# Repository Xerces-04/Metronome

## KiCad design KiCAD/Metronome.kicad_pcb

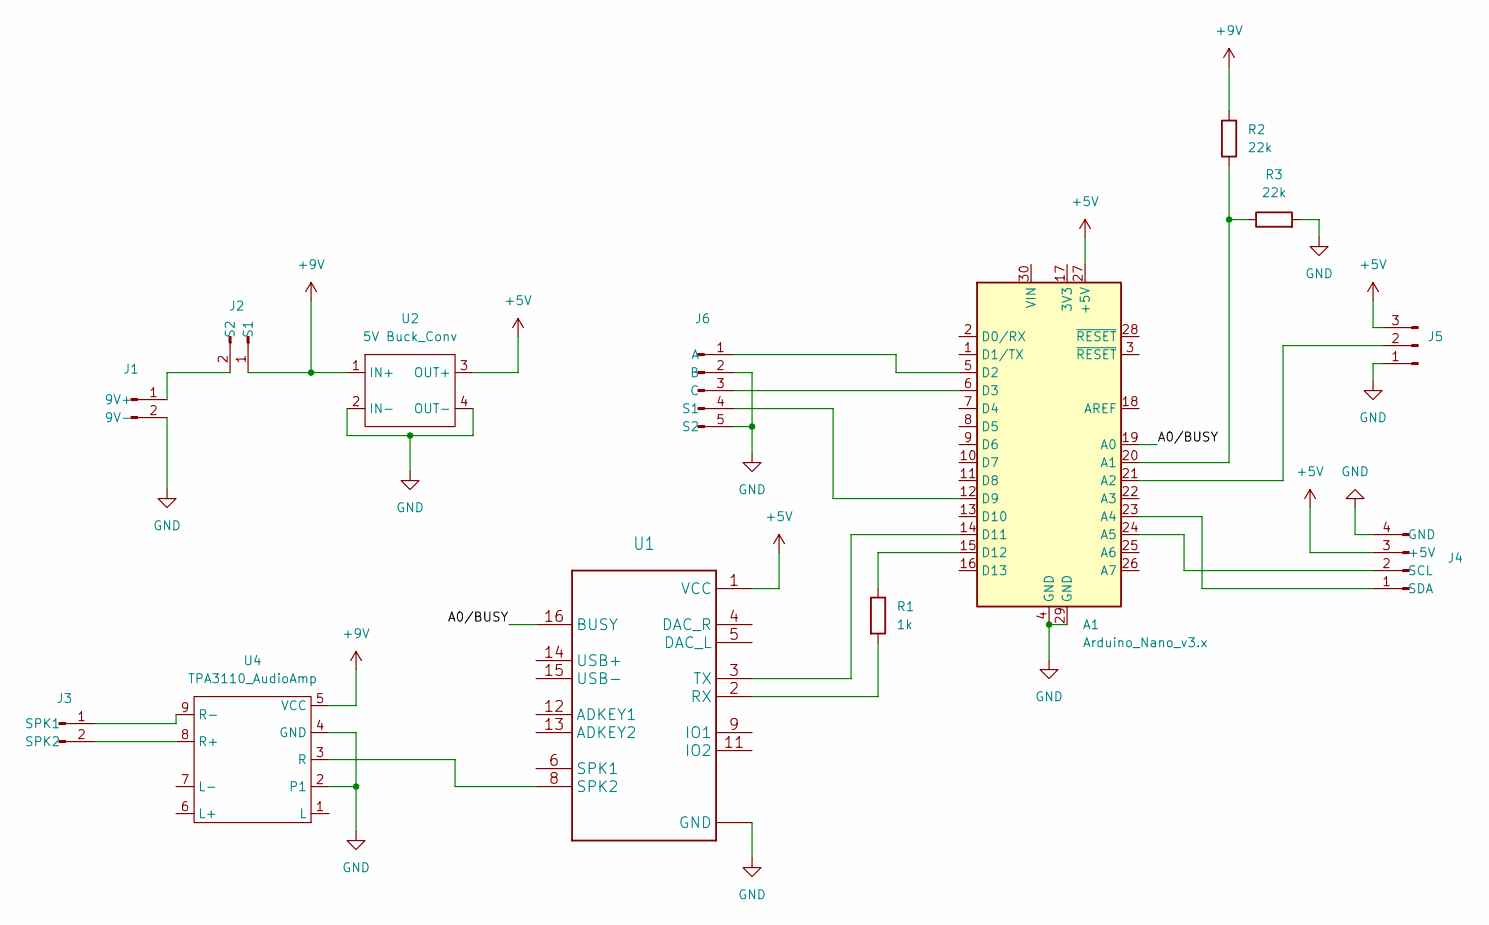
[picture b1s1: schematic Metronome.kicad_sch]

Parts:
A1: Arduino_Nano_v3.x; Arduino_Nano
J1, J2, J3: Conn_01x02_Pin; JST_XH_B2B-XH-A_1x02_P2.50mm_Vertical
J4: Conn_01x04_Pin; JST_XH_B4B-XH-A_1x04_P2.50mm_Vertical
J5: Conn_01x03_Pin; JST_XH_B3B-XH-A_1x03_P2.50mm_Vertical
J6: Conn_01x05_Pin; JST_XH_B5B-XH-A_1x05_P2.50mm_Vertical
R1: 1k; R_Axial_DIN0204_L3.6mm_D1.6mm_P7.62mm_Horizontal
R2, R3: 22k; R_Axial_DIN0204_L3.6mm_D1.6mm_P7.62mm_Horizontal
U1: MODULE_DFR0299
U2: 5V Buck_Conv; 5V_BuckConv
U4: TPA3110_AudioAmp

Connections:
+5V: A1.27 (+5V), J4.3 (+5V), J5.3, U1.1 (VCC), U2.3 (OUT+)
+9V: J2.1 (S1), R2.2, U2.1 (IN+), U4.5 (VCC)
/A0/BUSY: A1.19 (A0), U1.16 (BUSY)
GND: A1.4 (GND), A1.29 (GND), J1.2 (9V-), J4.4 (GND), J5.1, J6.2 (B), J6.5 (S2), R3.2, U1.7 (GND), U1.10 (GND), U2.2 (IN-), U2.4 (OUT-), U4.2 (P1), U4.4 (GND)
unnamed: A1.20 (A1), R2.1, R3.1
unnamed: A1.21 (A2), J5.2
unnamed: A1.23 (A4), J4.1 (SDA)
unnamed: A1.24 (A5), J4.2 (SCL)
unnamed: A1.5 (D2), J6.1 (A)
unnamed: A1.6 (D3), J6.3 (C)
unnamed: A1.12 (D9), J6.4 (S1)
unnamed: A1.14 (D11), U1.3 (TX)
unnamed: A1.15 (D12), R1.1
unnamed: J1.1 (9V+), J2.2 (S2)
unnamed: J3.1 (SPK1), U4.9 (R-)
unnamed: J3.2 (SPK2), U4.8 (R+)
unnamed: R1.2, U1.2 (RX)
unnamed: U1.8 (SPK2), U4.3 (R)

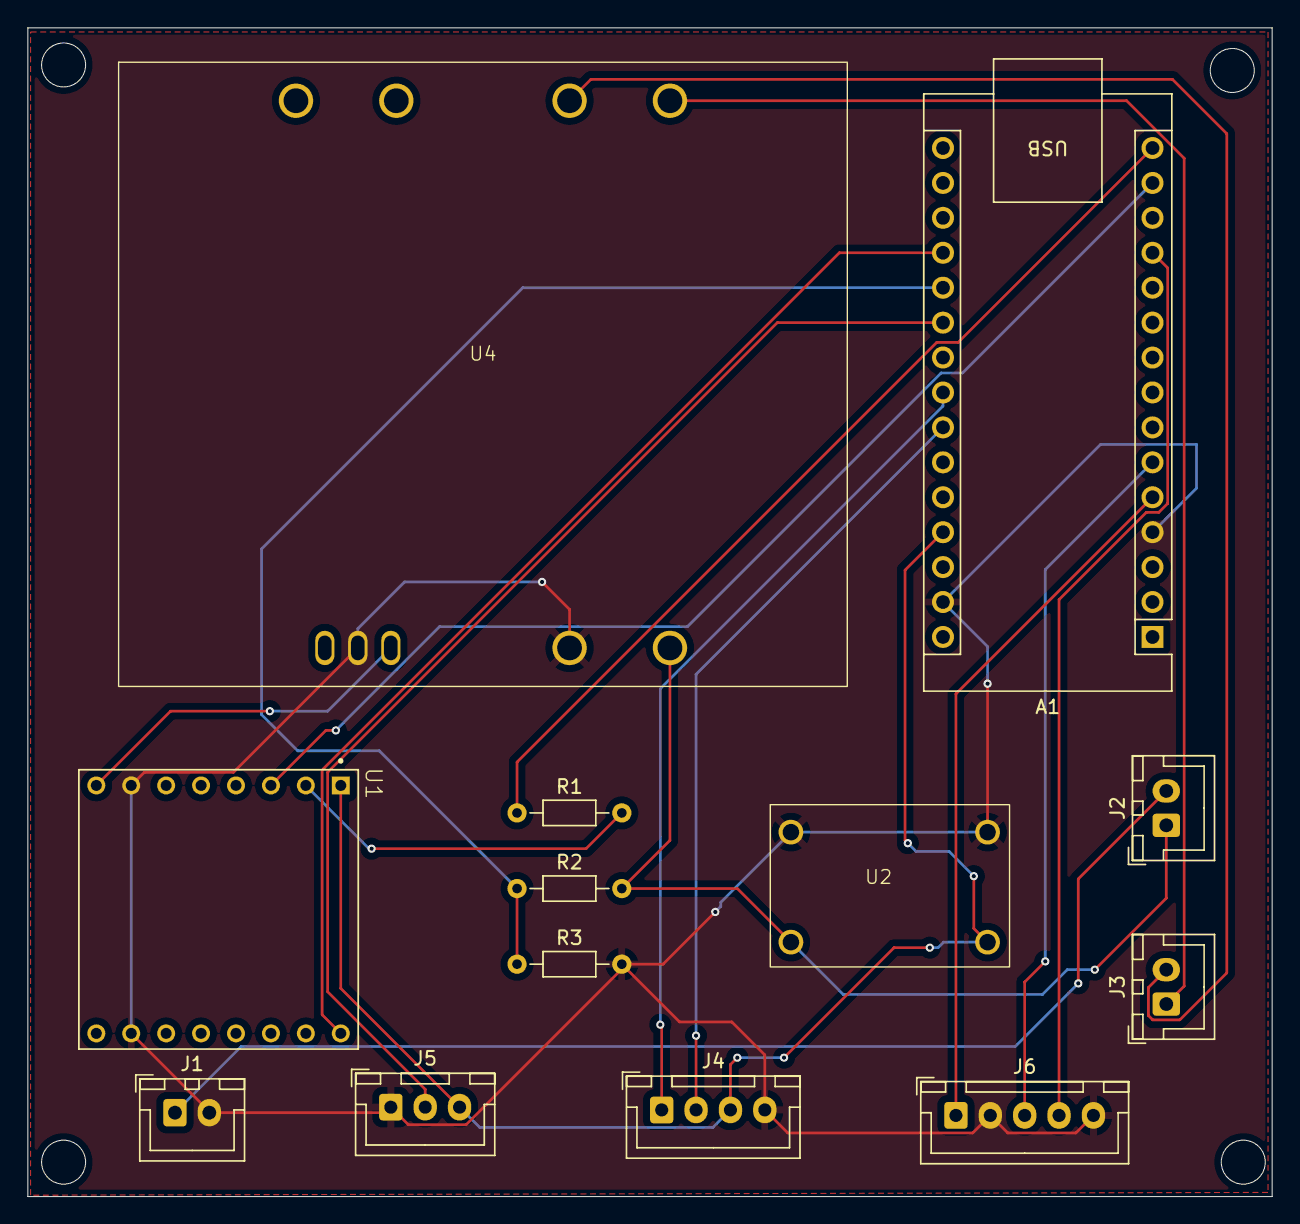
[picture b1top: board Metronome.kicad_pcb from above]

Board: 2 copper layers, 90.5 x 85.0 mm, 13 parts (0 on the bottom side), 18 nets.
